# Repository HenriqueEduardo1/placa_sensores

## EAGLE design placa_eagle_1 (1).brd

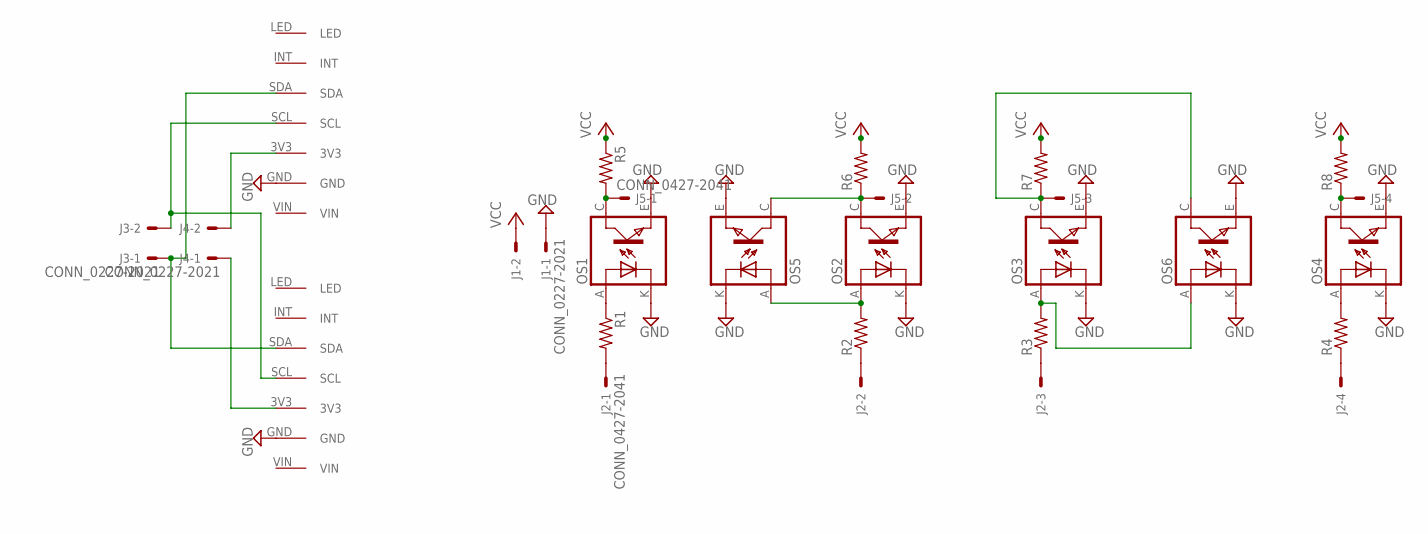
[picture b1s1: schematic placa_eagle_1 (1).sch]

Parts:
J1, J3, J4: CONN_0227-2021; 6410-02
J2, J5: CONN_0427-2041; 6410-04
OS1, OS2, OS3, OS4, OS5, OS6: TCRT5000
R1, R2, R3, R4, R5, R6, R7, R8: R-US_0204/7; 0204/7
TCS1, TCS2: TCS34725

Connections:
GND: J1.1, OS1.E (EMITTER), OS1.K (CATHODE), OS2.E (EMITTER), OS2.K (CATHODE), OS3.E (EMITTER), OS3.K (CATHODE), OS4.E (EMITTER), OS4.K (CATHODE), OS5.E (EMITTER), OS5.K (CATHODE), OS6.E (EMITTER), OS6.K (CATHODE), TCS1.GND, TCS2.GND
unnamed: OS1.A (ANODE), R1.1
unnamed: OS4.A (ANODE), R4.2
unnamed: J5.1, OS1.C (COLLECTOR), R5.2
unnamed: J5.4, OS4.C (COLLECTOR), R8.1
unnamed: J2.1, R1.2
unnamed: J2.2, R2.1
unnamed: J2.3, R3.1
unnamed: J2.4, R4.1
unnamed: J4.2, TCS1.3V3
unnamed: J4.1, TCS2.3V3
unnamed: OS2.A (ANODE), OS5.A (ANODE), R2.2
unnamed: J3.1, TCS1.SDA, TCS2.SDA
unnamed: J5.2, OS2.C (COLLECTOR), OS5.C (COLLECTOR), R6.1
unnamed: J3.2, TCS1.SCL, TCS2.SCL
unnamed: OS3.A (ANODE), OS6.A (ANODE), R3.2
unnamed: J5.3, OS3.C (COLLECTOR), OS6.C (COLLECTOR), R7.1
VCC: J1.2, R5.1, R6.2, R7.2, R8.2

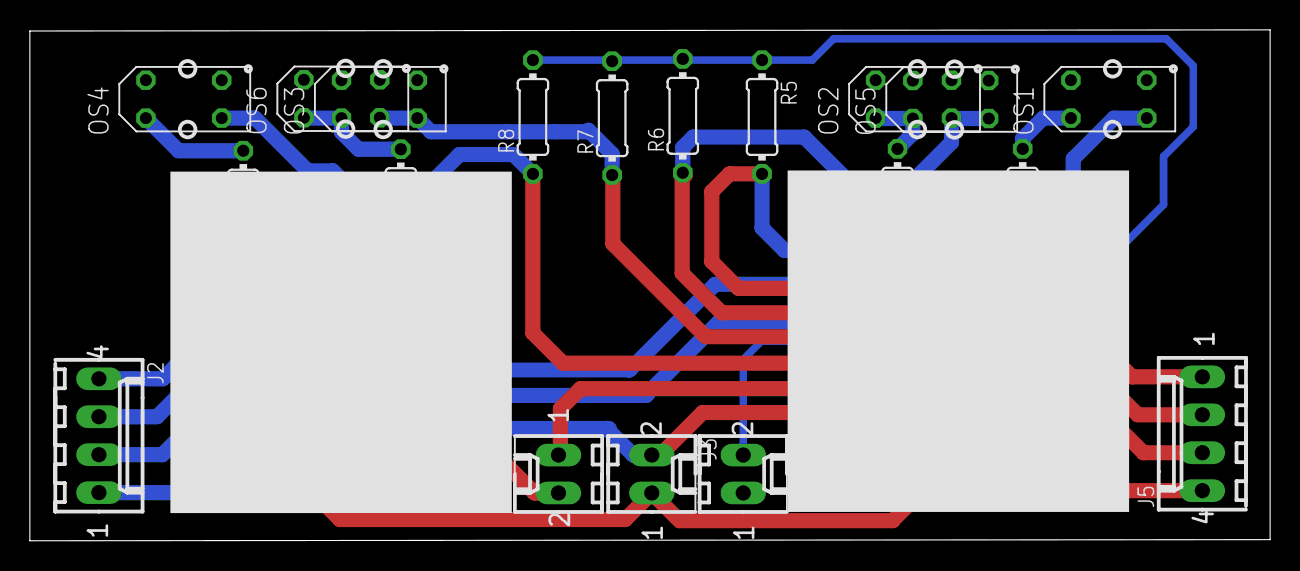
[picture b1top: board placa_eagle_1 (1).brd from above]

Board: 2 copper layers, 83.0 x 34.2 mm, 21 parts (0 on the bottom side), 18 nets.

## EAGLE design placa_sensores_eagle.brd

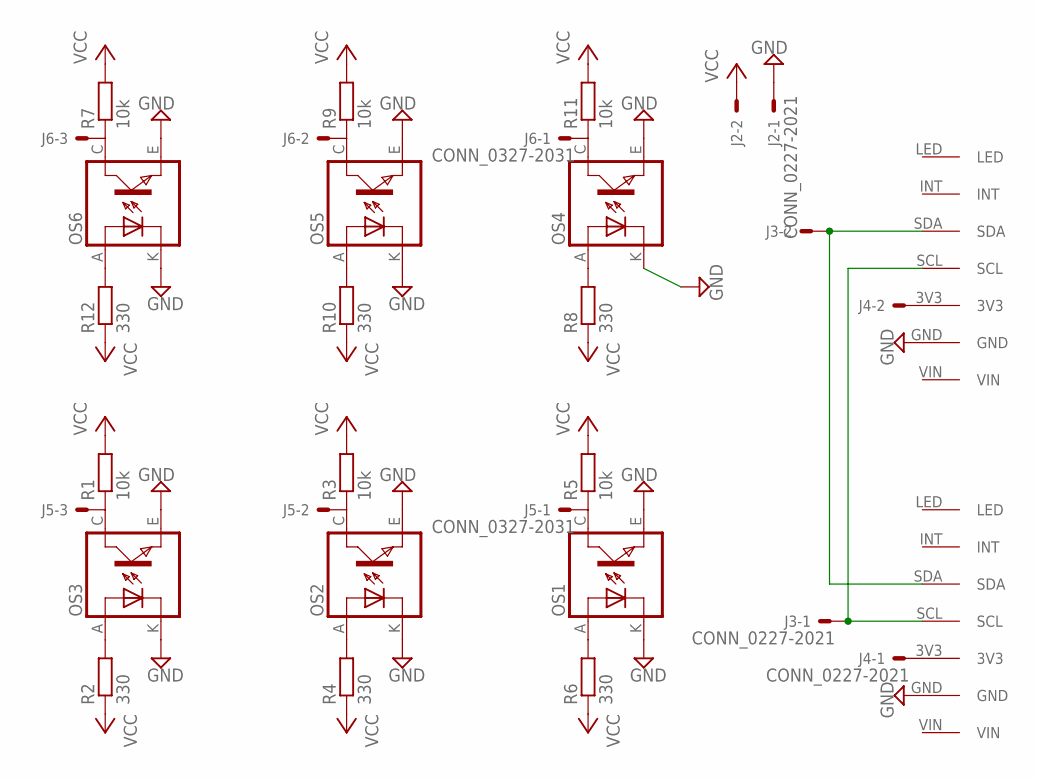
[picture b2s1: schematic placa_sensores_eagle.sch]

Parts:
J2, J3, J4: CONN_0227-2021; 6410-02
J5, J6: CONN_0327-2031; 6410-03
OS1, OS2, OS3, OS4, OS5, OS6: TCRT5000
R1, R3, R5, R7, R9, R11: 10k; 0204/7
R2, R4, R6, R8, R10, R12: 330; 0204/7
TCS1, TCS2: TCS34725

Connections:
GND: J2.1, OS1.E (EMITTER), OS1.K (CATHODE), OS2.E (EMITTER), OS2.K (CATHODE), OS3.E (EMITTER), OS3.K (CATHODE), OS4.E (EMITTER), OS4.K (CATHODE), OS5.E (EMITTER), OS5.K (CATHODE), OS6.E (EMITTER), OS6.K (CATHODE), TCS1.GND, TCS2.GND
unnamed: J5.1, OS1.C (COLLECTOR), R5.1
unnamed: OS5.A (ANODE), R10.2
unnamed: J6.1, OS4.C (COLLECTOR), R11.1
unnamed: J6.2, OS5.C (COLLECTOR), R9.1
unnamed: J6.3, OS6.C (COLLECTOR), R7.1
unnamed: OS6.A (ANODE), R12.2
unnamed: J5.2, OS2.C (COLLECTOR), R3.1
unnamed: J5.3, OS3.C (COLLECTOR), R1.1
unnamed: OS1.A (ANODE), R6.2
unnamed: OS2.A (ANODE), R4.2
unnamed: OS3.A (ANODE), R2.2
unnamed: J3.2, TCS1.SDA, TCS2.SDA
unnamed: J3.1, TCS1.SCL, TCS2.SCL
unnamed: J4.2, TCS1.3V3
unnamed: J4.1, TCS2.3V3
unnamed: OS4.A (ANODE), R8.2
VCC: J2.2, R1.2, R2.1, R3.2, R4.1, R5.2, R6.1, R7.2, R8.1, R9.2, R10.1, R11.2, R12.1

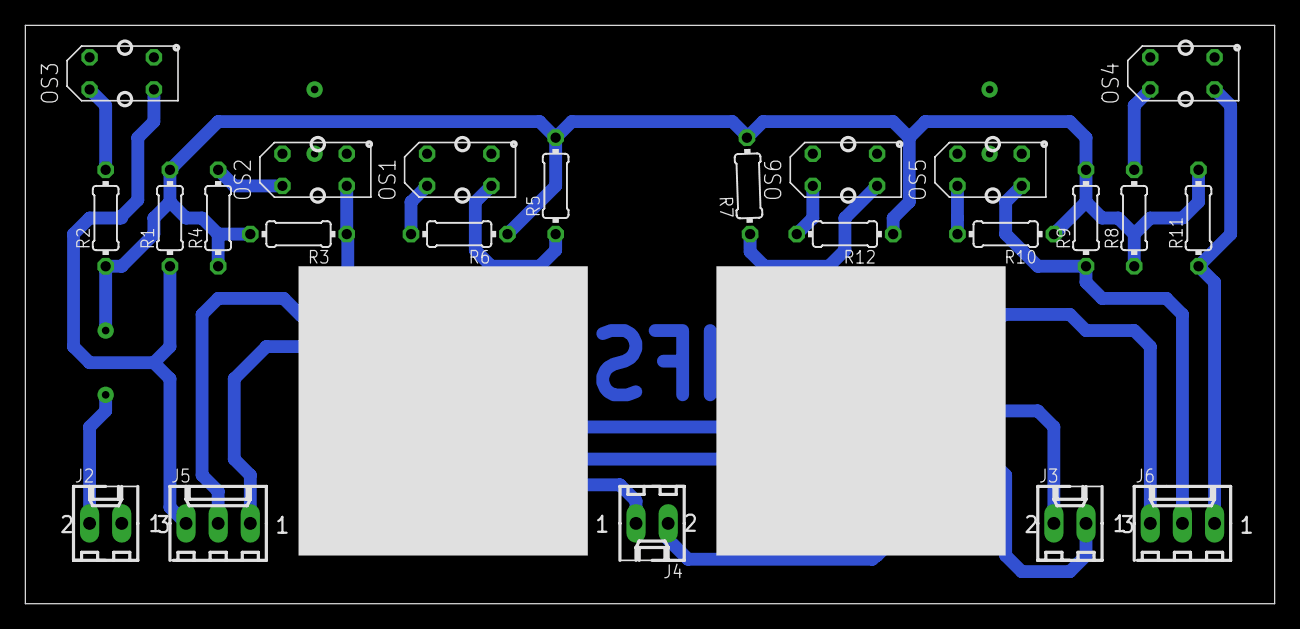
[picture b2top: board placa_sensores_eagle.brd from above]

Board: 2 copper layers, 98.7 x 45.7 mm, 25 parts (0 on the bottom side), 18 nets.

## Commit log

2018-09-10 Placa de sensores eagle
2018-09-10 ignore commited
2018-09-10 foi apagado uma seta
2019-03-11 Placa:
    foi alterado a distância dos sensores.
2019-03-11 Placa:
    foi ajustada a posição dos conectores.
2019-03-21 praca china:
    foi ajustado a posição dos conectores.
2019-03-29 Placa ataulizada.
2019-04-01 Adição de logos
    Adição dos logos do IFRN e da robótica.
    Adição do texto com a versão da placa
2019-04-08 Placa:
    foi adicionado os furos na paca.
